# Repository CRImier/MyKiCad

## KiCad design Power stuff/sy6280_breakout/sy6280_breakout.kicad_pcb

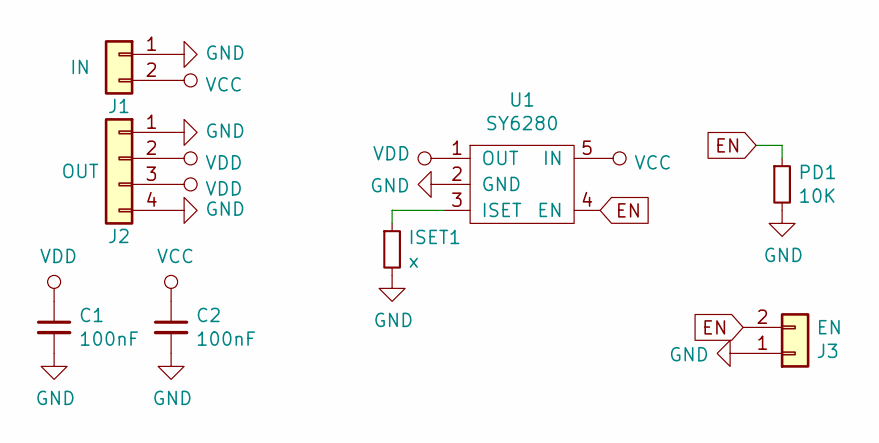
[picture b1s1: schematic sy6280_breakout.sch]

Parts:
C1, C2: 100nF; C_0805_2012Metric
ISET1: x; R_0805_2012Metric_Pad1.15x1.40mm_HandSolder
J1: IN; PinHeader_1x02_P2.54mm_Vertical
J2: OUT; PinHeader_1x04_P2.54mm_Vertical
J3: EN; PinHeader_1x02_P2.54mm_Vertical
PD1: 10K; R_0805_2012Metric_Pad1.15x1.40mm_HandSolder
U1: SY6280; SOT-23-5

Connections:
EN: J3.2, PD1.1, U1.4 (EN)
GND: C1.2, C2.2, ISET1.2, J1.1, J2.1, J2.4, J3.1, PD1.2, U1.2 (GND)
unnamed: ISET1.1, U1.3 (ISET)
VCC: C2.1, J1.2, U1.5 (IN)
VDD: C1.1, J2.2, J2.3, U1.1 (OUT)

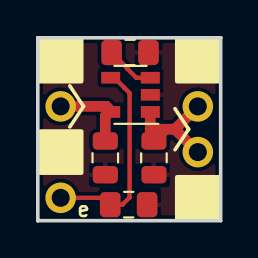
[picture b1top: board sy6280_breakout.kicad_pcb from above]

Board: 2 copper layers, 10.2 x 10.2 mm, 8 parts (0 on the bottom side), 5 nets.

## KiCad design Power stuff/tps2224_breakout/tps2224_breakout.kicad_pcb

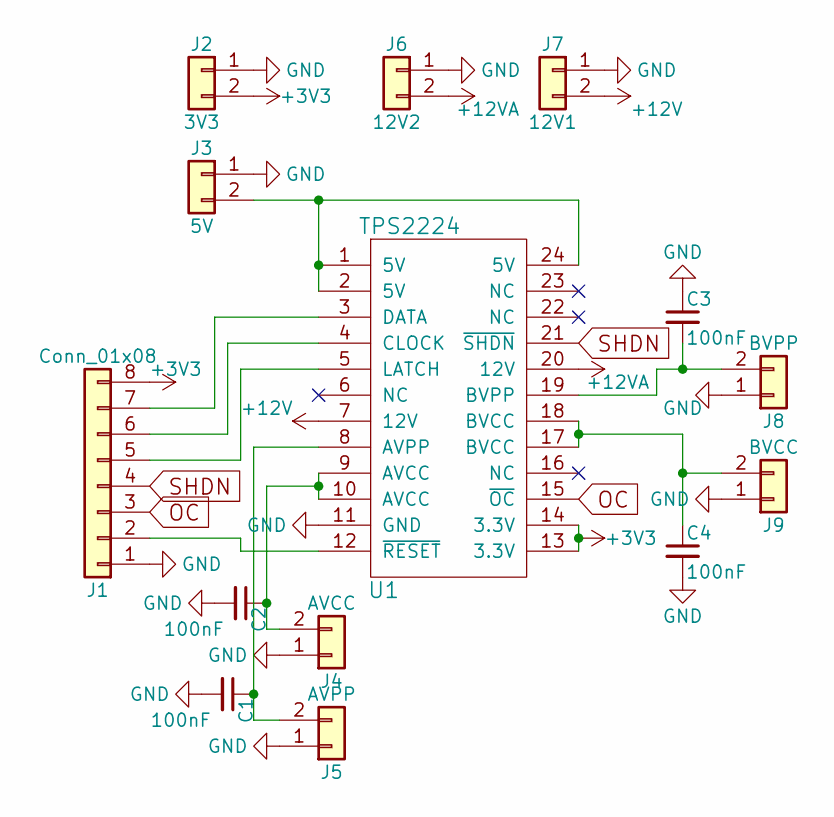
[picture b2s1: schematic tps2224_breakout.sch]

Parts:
C1, C2, C3, C4: 100nF; C_0805
J1: Conn_01x08; Pin_Header_Straight_1x08_Pitch2.54mm
J2: 3V3; Pin_Header_Straight_1x02_Pitch2.54mm
J3: 5V; Pin_Header_Straight_1x02_Pitch2.54mm
J4: AVCC; Pin_Header_Straight_1x02_Pitch2.54mm
J5: AVPP; Pin_Header_Straight_1x02_Pitch2.54mm
J6: 12V2; Pin_Header_Straight_1x02_Pitch2.54mm
J7: 12V1; Pin_Header_Straight_1x02_Pitch2.54mm
J8: BVPP; Pin_Header_Straight_1x02_Pitch2.54mm
J9: BVCC; Pin_Header_Straight_1x02_Pitch2.54mm
U1: TPS2224; TSSOP-24_4.4x7.8mm_Pitch0.65mm

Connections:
+3V3: J1.8, J2.2, U1.13 (3.3V), U1.14 (3.3V)
+12V: J7.2, U1.7 (12V)
+12VA: J6.2, U1.20 (12V)
GND: C1.2, C2.2, C3.1, C4.2, J1.1, J2.1, J3.1, J4.1, J5.1, J6.1, J7.1, J8.1, J9.1, U1.11 (GND)
unnamed: C1.1, J5.2, U1.8 (AVPP)
unnamed: C2.1, J4.2, U1.9 (AVCC), U1.10 (AVCC)
unnamed: C3.2, J8.2, U1.19 (BVPP)
unnamed: C4.1, J9.2, U1.17 (BVCC), U1.18 (BVCC)
unnamed: J1.2, U1.12 (~RESET)
unnamed: J1.5, U1.5 (LATCH)
unnamed: J1.6, U1.4 (CLOCK)
unnamed: J1.7, U1.3 (DATA)
unnamed: J3.2, U1.1 (5V), U1.2 (5V), U1.24 (5V)
OC: J1.3, U1.15 (~OC)
SHDN: J1.4, U1.21 (~SHDN)

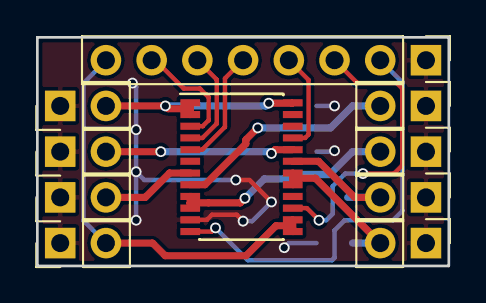
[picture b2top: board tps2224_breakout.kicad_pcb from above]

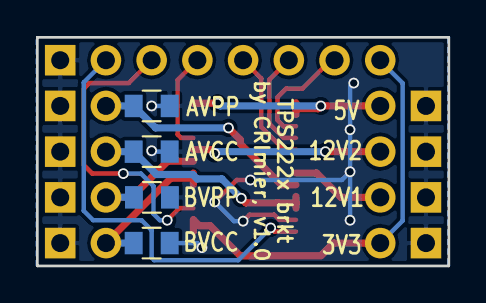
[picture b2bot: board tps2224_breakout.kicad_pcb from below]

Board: 2 copper layers, 22.9 x 12.7 mm, 14 parts (4 on the bottom side), 15 nets.

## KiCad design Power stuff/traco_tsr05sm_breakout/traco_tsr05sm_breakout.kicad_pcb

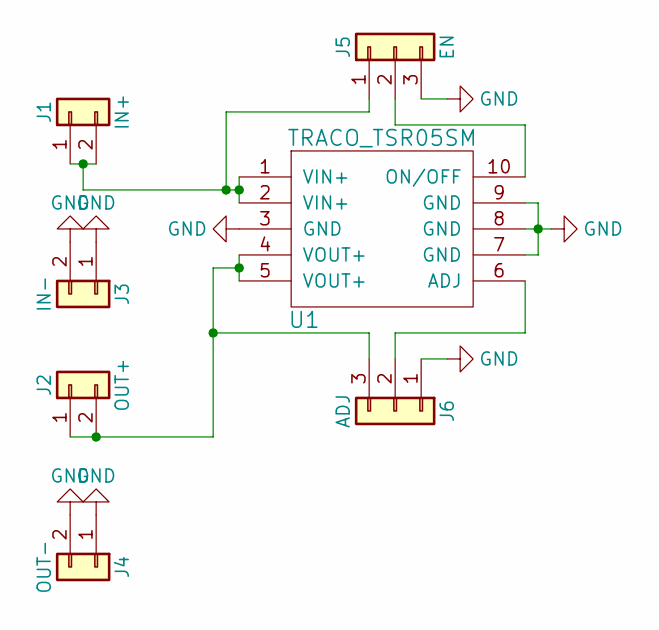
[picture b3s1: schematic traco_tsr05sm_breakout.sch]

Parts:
J1: IN+; WireConnection_2.00mmDrill
J2: OUT+; WireConnection_2.00mmDrill
J3: IN-; WireConnection_2.00mmDrill
J4: OUT-; WireConnection_2.00mmDrill
J5: EN; Pin_Header_Straight_1x03_Pitch2.54mm
J6: ADJ; Pin_Header_Straight_1x03_Pitch2.54mm
U1: TRACO_TSR05SM

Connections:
GND: J3.1, J3.2, J4.1, J4.2, J5.3, J6.1, U1.3 (GND), U1.7 (GND), U1.8 (GND), U1.9 (GND)
unnamed: J1.1, J1.2, J5.1, U1.1 (VIN+), U1.2 (VIN+)
unnamed: J2.1, J2.2, J6.3, U1.4 (VOUT+), U1.5 (VOUT+)
unnamed: J5.2, U1.10 (ON/OFF)
unnamed: J6.2, U1.6 (ADJ)

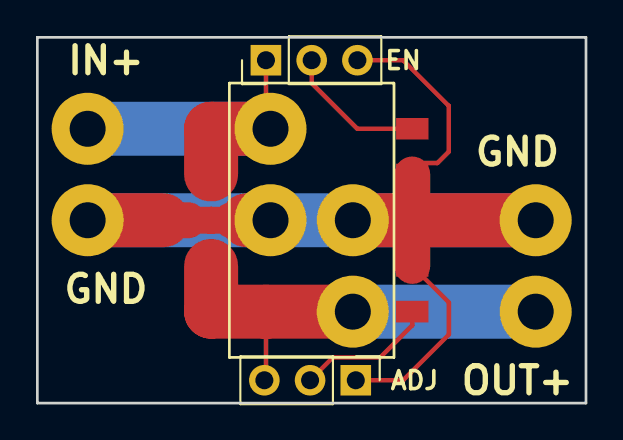
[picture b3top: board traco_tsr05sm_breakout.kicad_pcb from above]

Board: 2 copper layers, 30.5 x 20.3 mm, 7 parts (0 on the bottom side), 5 nets.

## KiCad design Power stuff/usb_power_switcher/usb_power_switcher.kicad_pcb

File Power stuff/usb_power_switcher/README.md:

# USB power switcher

This is a board that switches a USB power signal by using a P-FET to interrupt it. This way,
you can control power to a USB device of your choosing. You can also choose to interrupt the
D- or D+ signals manually, by cutting the jumpers on the bottom of the board.
It has LEDs for output and input power state indication, as well as control signal state.

This board has a MicroUSB input and a USB-A female output. 
It could possibly have a USB-A input plug, but I never tested its polarity.
For now, I personally use the USB-A input for soldering wires to, as a rule.

Jumper signals are arranged in a way that you can use a single 2.54mm jumper to switch the board's state.
There's no overcurrent protection on the board - so be careful.

Signal names are silkscreened on the board's bottom layer.

- PCB size: 36.22*h
- Layer count: 2
- Recommended thickness: t

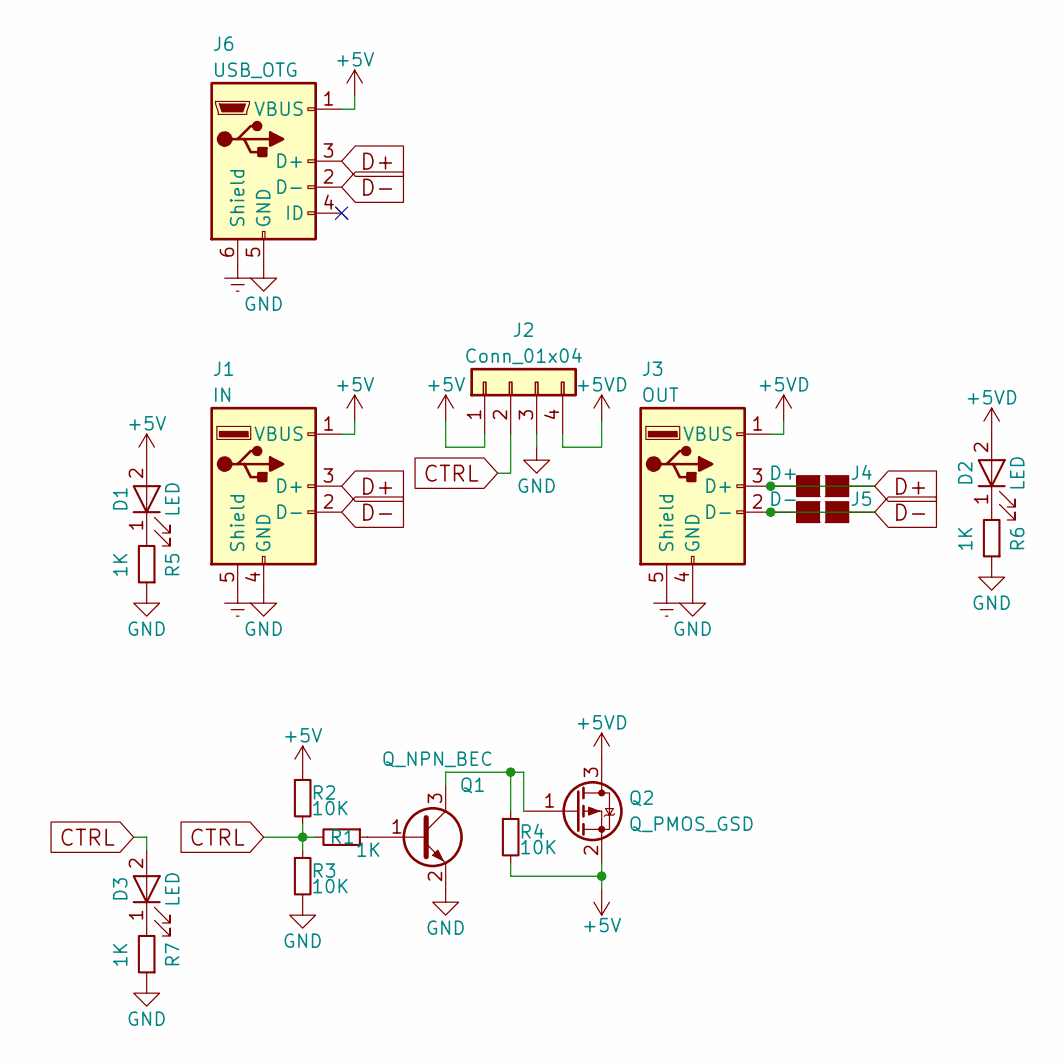
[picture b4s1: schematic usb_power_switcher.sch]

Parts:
D1, D2, D3: LED; LED_0805_HandSoldering
J1: IN; USB_A
J2: Conn_01x04; Pin_Header_Straight_1x04_Pitch2.54mm
J3: OUT; USB_A
J4: D+; GS2_SMALL
J5: D-; GS2_SMALL
J6: USB_OTG; MICROUSB_SIMPLE
Q1: Q_NPN_BEC; SOT-23_Handsoldering
Q2: Q_PMOS_GSD; SOT-23_Handsoldering
R1, R5, R6, R7: 1K; R_0603_HandSoldering
R2, R3, R4: 10K; R_0603_HandSoldering

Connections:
+5V: D1.2 (A), J1.1 (VBUS), J2.1, J6.1 (VBUS), Q2.2 (S), R2.1, R4.2
+5VD: D2.2 (A), J2.4, J3.1 (VBUS), Q2.3 (D)
CTRL: D3.2 (A), J2.2, R1.2, R2.2, R3.1
D+: J1.3 (D+), J3.3 (D+), J4.1 (G1), J4.2 (G2), J6.3 (D+)
D-: J1.2 (D-), J3.2 (D-), J5.1 (G1), J5.2 (G2), J6.2 (D-)
Earth: J1.5 (Shield), J3.5 (Shield), J6.6 (Shield)
GND: J1.4 (GND), J2.3, J3.4 (GND), J6.5 (GND), Q1.2 (E), R3.2, R5.1, R6.1, R7.1
unnamed: D1.1 (K), R5.2
unnamed: D2.1 (K), R6.2
unnamed: D3.1 (K), R7.2
unnamed: Q1.1 (B), R1.1
unnamed: Q1.3 (C), Q2.1 (G), R4.1

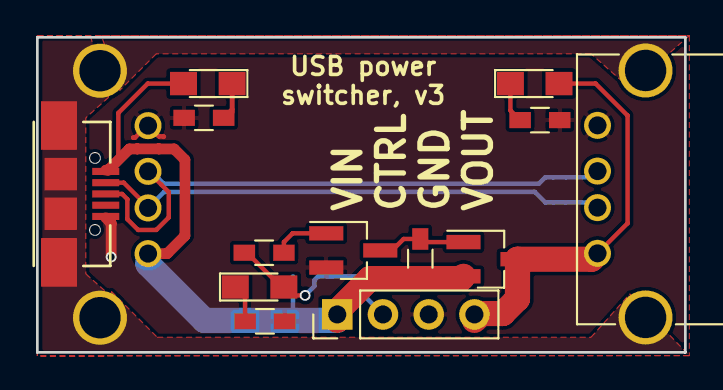
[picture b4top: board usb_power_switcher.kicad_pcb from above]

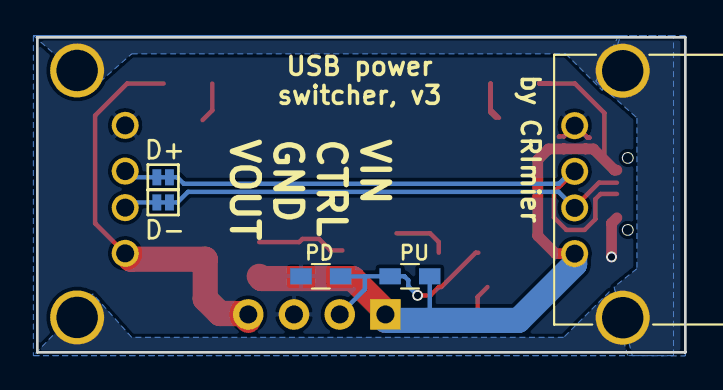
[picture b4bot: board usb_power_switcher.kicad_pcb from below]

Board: 2 copper layers, 36.0 x 17.5 mm, 18 parts (5 on the bottom side), 12 nets.

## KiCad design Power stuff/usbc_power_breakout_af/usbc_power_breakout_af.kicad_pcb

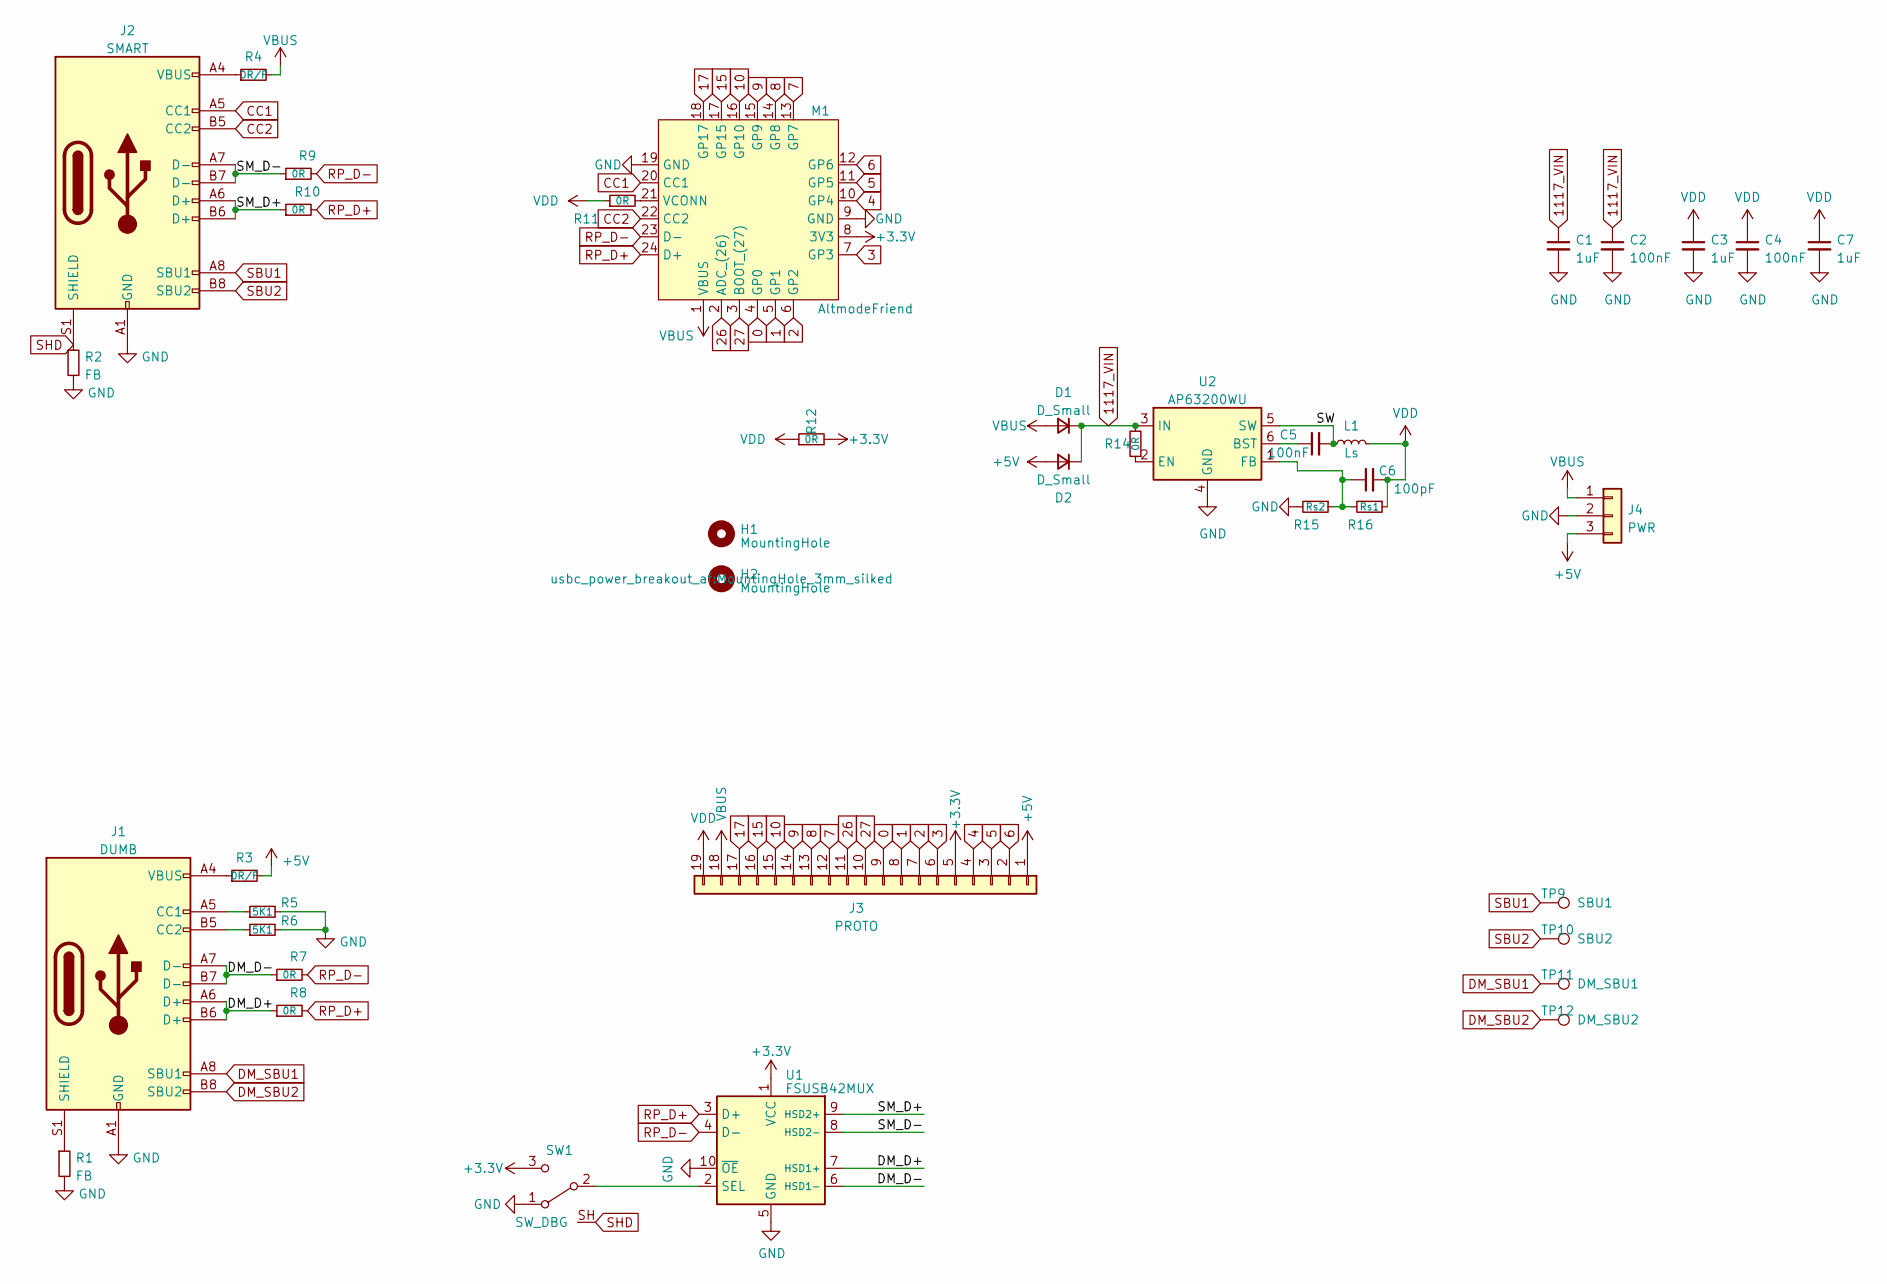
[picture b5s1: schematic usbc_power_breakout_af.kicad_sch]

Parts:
C1, C3, C7: 1uF; C_0805_2012Metric
C2: 100nF; C_0805_2012Metric
C4, C5: 100nF; C_0603_1608Metric
C6: 100pF; C_0603_1608Metric
D1, D2: D_Small; D_SMA
H1, H2: MountingHole; MountingHole_3mm_silked
J1: DUMB; USB_C_Receptacle_HRO_TYPE-C-31-M-12
J2: SMART; USB_C_Receptacle_HRO_TYPE-C-31-M-12
J3: PROTO; PROTO_THT_SMD_4x
J4: PWR; PinHeader_1x03_P2.54mm_Vertical
L1: Ls; L_Bourns-SRN4018
M1: AltmodeFriend; altmode_friend
R1, R2: FB; R_0805_2012Metric
R3, R4: 0R/F; R_0805_2012Metric
R5, R6: 5K1; R_0603_1608Metric
R7, R8, R9, R10, R11, R12, R14: 0R; R_0603_1608Metric
R15: Rs2; R_0603_1608Metric
R16: Rs1; R_0603_1608Metric
SW1: SW_DBG; SW_SPDT_PCM12_SH
TP9: SBU1; TestPoint_THTPad_D1.0mm_Drill0.5mm
TP10: SBU2; TestPoint_THTPad_D1.0mm_Drill0.5mm
TP11: DM_SBU1; TestPoint_THTPad_1.5x1.5mm_Drill0.7mm
TP12: DM_SBU2; TestPoint_THTPad_1.5x1.5mm_Drill0.7mm
U1: FSUSB42MUX; MSOP-10_3x3mm_P0.5mm
U2: AP63200WU; TSOT-23-6

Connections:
0: J3.9, M1.4 (GP0)
1: J3.8, M1.5 (GP1)
2: J3.7, M1.6 (GP2)
3: J3.6, M1.7 (GP3)
4: J3.4, M1.10 (GP4)
5: J3.3, M1.11 (GP5)
6: J3.2, M1.12 (GP6)
7: J3.12, M1.13 (GP7)
8: J3.13, M1.14 (GP8)
9: J3.14, M1.15 (GP9)
10: J3.15, M1.16 (GP10)
15: J3.16, M1.17 (GP15)
17: J3.17, M1.18 (GP17)
26: J3.11, M1.2 (ADC_(26))
27: J3.10, M1.3 (BOOT_(27))
1117_VIN: C1.1, C2.1, D1.1 (K), D2.1 (K), R14.2, U2.3 (IN)
+5V: D2.2 (A), J3.1, J4.3, R3.2
/DM_D+: J1.A6 (D+), J1.B6 (D+), R8.1, U1.7 (HSD1+)
/DM_D-: J1.A7 (D-), J1.B7 (D-), R7.1, U1.6 (HSD1-)
/SM_D+: J2.A6 (D+), J2.B6 (D+), R10.1, U1.9 (HSD2+)
/SM_D-: J2.A7 (D-), J2.B7 (D-), R9.1, U1.8 (HSD2-)
/SW: C5.2, L1.1, U2.5 (SW)
CC1: J2.A5 (CC1), M1.20 (CC1)
CC2: J2.B5 (CC2), M1.22 (CC2)
DM_SBU1: J1.A8 (SBU1), TP11.1
DM_SBU2: J1.B8 (SBU2), TP12.1
GND: C1.2, C2.2, C3.2, C4.2, C7.2, J1.A1 (GND), J1.A12 (GND), J1.B1 (GND), J1.B12 (GND), J2.A1 (GND), J2.A12 (GND), J2.B1 (GND), J2.B12 (GND), J4.2, M1.9 (GND), M1.19 (GND), R1.2, R2.2, R5.2, R6.2, R15.2, SW1.1 (A), U1.5 (GND), U1.10 (~OE), U2.4 (GND)
unnamed: J1.A5 (CC1), R5.1
unnamed: J1.B5 (CC2), R6.1
unnamed: J1.S1 (SHIELD), R1.1
unnamed: J1.A4 (VBUS), J1.A9 (VBUS), J1.B4 (VBUS), J1.B9 (VBUS), R3.1
unnamed: J2.A4 (VBUS), J2.A9 (VBUS), J2.B4 (VBUS), J2.B9 (VBUS), R4.1
unnamed: M1.21 (VCONN), R11.2
unnamed: SW1.2 (B), U1.2 (SEL)
unnamed: C5.1, U2.6 (BST)
unnamed: R14.1, U2.2 (EN)
unnamed: C6.1, R15.1, R16.2, U2.1 (FB)
RP_D+: M1.24 (D+), R8.2, R10.2, U1.3 (D+)
RP_D-: M1.23 (D-), R7.2, R9.2, U1.4 (D-)
SBU1: J2.A8 (SBU1), TP9.1
SBU2: J2.B8 (SBU2), TP10.1
SHD: J2.S1 (SHIELD), R2.1, SW1.SH
VBUS: D1.2 (A), J3.18, J4.1, M1.1 (VBUS), R4.2
VDD: C3.1, C4.1, C6.2, C7.1, J3.19, L1.2, R11.1, R12.1, R16.1

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
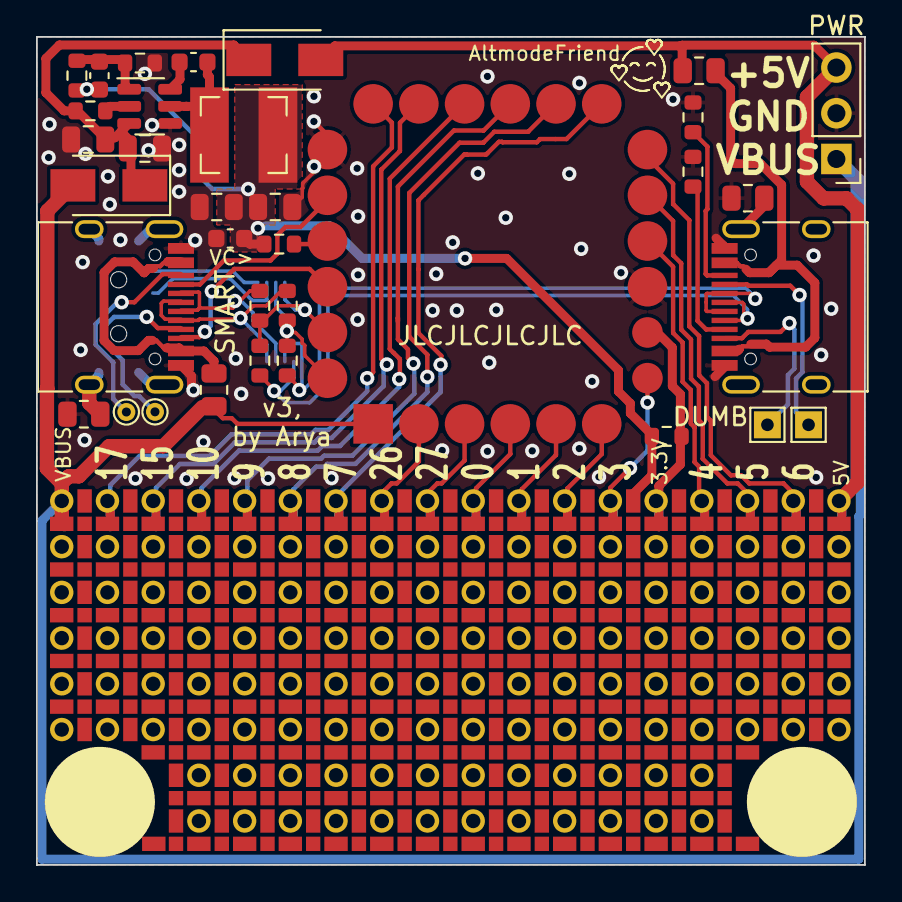
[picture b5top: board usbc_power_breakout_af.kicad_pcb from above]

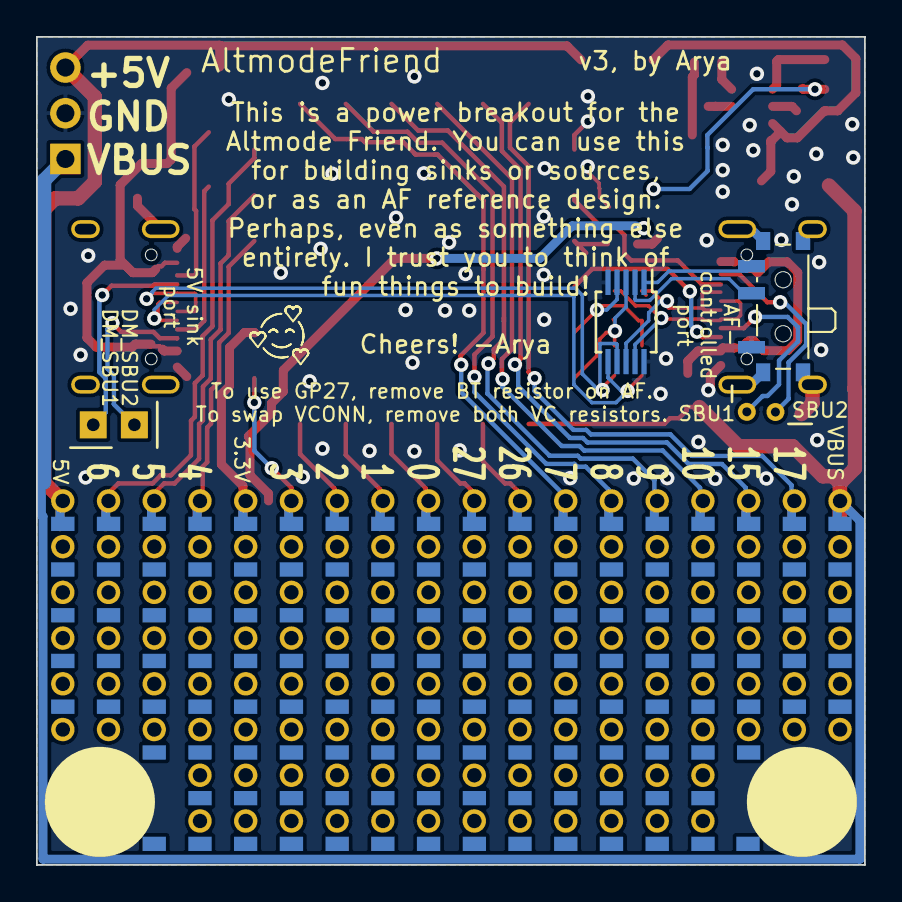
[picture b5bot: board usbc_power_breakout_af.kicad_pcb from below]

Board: 2 copper layers, 46.0 x 46.0 mm, 39 parts (2 on the bottom side), 46 nets.

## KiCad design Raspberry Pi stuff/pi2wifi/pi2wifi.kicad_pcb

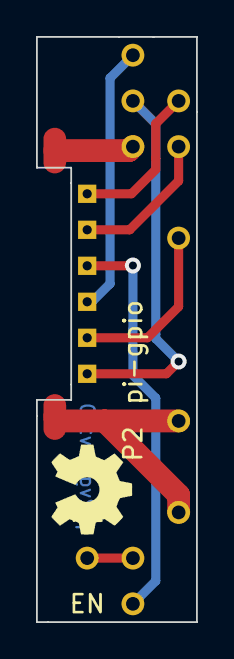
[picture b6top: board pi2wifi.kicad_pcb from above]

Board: 2 copper layers, 8.9 x 32.5 mm, 3 parts (0 on the bottom side), 9 nets.

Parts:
P1: EN; TP
P2: pi-gpio
U1: ESP-12F; ESP-12-F

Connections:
unnamed: P1.1, P2.35
unnamed: P2.37, U1.11
unnamed: P2.16, U1.9
unnamed: P2.18, U1.10
unnamed: P2.15, U1.14
unnamed: P2.13, U1.12
unnamed: P2.22, U1.13
unnamed: P2.30, P2.34, U1.15
unnamed: P2.17, U1.8

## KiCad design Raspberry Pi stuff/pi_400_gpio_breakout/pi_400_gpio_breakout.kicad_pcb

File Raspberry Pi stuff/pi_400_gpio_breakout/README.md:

# Raspberry Pi 400 GPIO adapter board

This board is designed to be plugged into a Raspberry Pi 400 and allow to plug a HAT into your Pi 400 the same way that
you'd plug a hat onto your Raspberry Pi. Apart from that, it also has 2 QWIIC connectors, one 5-pin I2C pin header
with an extra GPIO (same pinout as Pi pins 1-9) and one custom-pinout pin header with SPI, I2S, 3.3V and 5V (same pinout
as the ZeroPhone expansion header pinout).

For ease of routing purposes, this is a 4-layer board, but it could probably be re-routed into a 2-layer board
if someone were willing to spend time on that. Sadly, the Pi 400 GPIO header pin assignment doesn't make for straightforward routing
when it comes to the connector placement I've devised, and I don't need this to be a 2-layer board at the moment.
Let me know if you want to make it into one - I can help you understand how to route it.

For custom connectors with I2C, SPI and I2S, signal names are silkscreened on the board's top layer, including the QWIIC pinout.

v1.0:
    - Initial commit
v2
    - stencil remains the same as in v1.0
    - enlarged mounting holes to 3.2mm
    - small routing mistakes fixed
    - changed I2C header footprint and moved it closer to the board edge

- PCB size: 55*60mm
- Layer count: 4
- Recommended thickness: 1.6mm (it's a relatively large board and has to hold up well to bending)

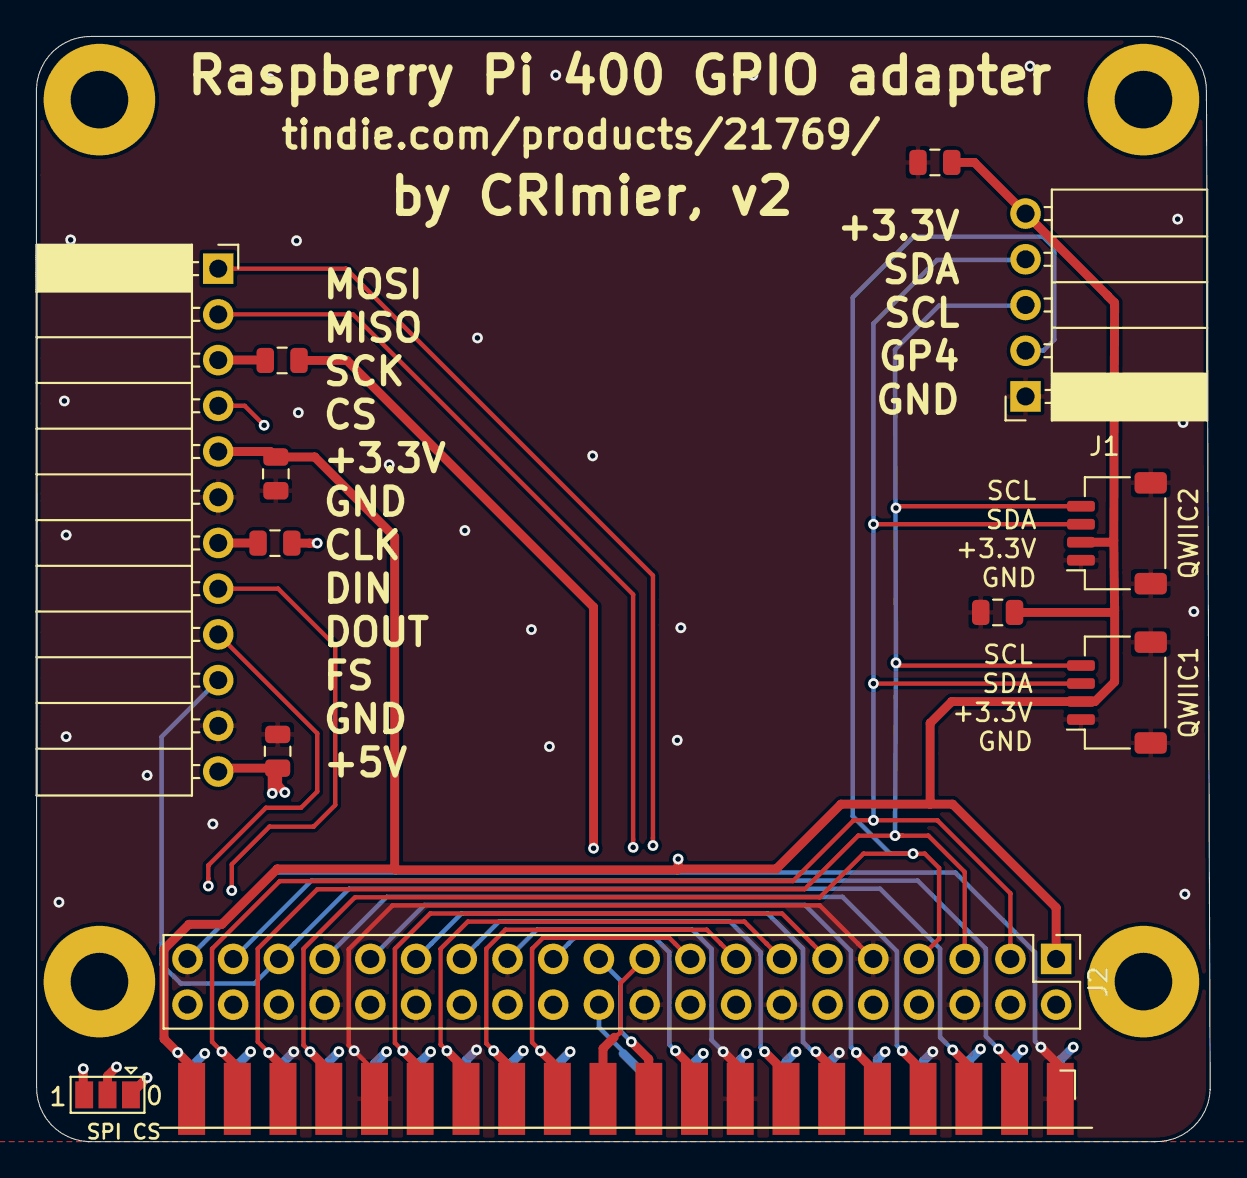
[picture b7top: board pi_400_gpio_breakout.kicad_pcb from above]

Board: 4 copper layers, 65.2 x 61.4 mm, 14 parts (0 on the bottom side), 34 nets.

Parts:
C1, C2, C3, C4: 100nF; C_0805_2012Metric
J1: I2C; PinSocket_1x05_P2.54mm_Horizontal
J2: RPI_IN; PinHeader_2x20_P2.54mm_Vertical
J3: SPI_I2S; PinSocket_1x12_P2.54mm_Horizontal
J4: QWIIC1; JST_SH_SM04B-SRSS-TB_1x04-1MP_P1.00mm_Horizontal
J5: Raspberry_Pi_2_3; RASPBERRY_PI_HAT
J5#2: RPI_IN; Side_2x20_Connector_SMD
J6: QWIIC2; JST_SH_SM04B-SRSS-TB_1x04-1MP_P1.00mm_Horizontal
JP1: SPI CS; SolderJumper-3_P1.3mm_Open_Pad1.0x1.5mm
R1, R2: 47R; R_0805_2012Metric

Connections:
+3V3: C1.1, C2.1, C3.1, J1.5, J2.1, J2.17, J3.5, J4.2, J5#2.1, J5#2.17, J6.2
+5V: C4.1, J2.2, J2.4, J3.12, J5#2.2, J5#2.4
/CS: J3.4, JP1.2
/CS0: J2.24, J5#2.24, JP1.1
/CS1: J2.26, J5#2.26, JP1.3
/GP4: J1.2, J2.7, J5#2.7
/MISO: J2.21, J3.2, J5#2.21
/MOSI: J2.19, J3.1, J5#2.19
/PCM_CLK: J2.18, J5#2.18, R2.1
/PCM_DIN: J2.38, J3.8, J5#2.38
/PCM_DOUT: J2.40, J3.9, J5#2.40
/PCM_FS: J2.35, J3.10, J5#2.35
/SCK: J2.23, J5#2.23, R1.1
/SCL: J1.3, J2.5, J4.4, J5#2.5, J6.4
/SDA: J1.4, J2.3, J4.3, J5#2.3, J6.3
GND: C1.2, C2.2, C3.2, C4.2, J1.1, J2.6, J2.9, J2.14, J2.20, J2.25, J2.30, J2.34, J2.39, J3.6, J3.11, J4.1, J4.MP, J5#2.6, J5#2.9, J5#2.14, J5#2.20, J5#2.25, J5#2.30, J5#2.34, J5#2.39, J6.1, J6.MP
unnamed: J2.8, J5#2.8
unnamed: J2.10, J5#2.10
unnamed: J2.11, J5#2.11
unnamed: J2.12, J5#2.12
unnamed: J2.13, J5#2.13
unnamed: J2.15, J5#2.15
unnamed: J2.16, J5#2.16
unnamed: J2.22, J5#2.22
unnamed: J2.27, J5#2.27
unnamed: J2.28, J5#2.28
unnamed: J2.29, J5#2.29
unnamed: J2.31, J5#2.31
unnamed: J2.32, J5#2.32
unnamed: J2.33, J5#2.33
unnamed: J2.36, J5#2.36
unnamed: J2.37, J5#2.37
unnamed: J3.3, R1.2
unnamed: J3.7, R2.2

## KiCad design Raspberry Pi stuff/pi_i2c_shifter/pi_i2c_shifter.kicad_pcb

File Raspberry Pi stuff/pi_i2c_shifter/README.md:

# Pi I2C shifter

This board level-shifts the I2C header and the GPIO to 5V using a N-FET level shifter approach.
It can be mounted to the Pi in two different orientation, so that the 5V I2C header can either stick
outside of the Pi outline or stay inside of it for a compact build.

Pin headers are arranged in a way that this board can be plugged into a breadboard from the I2C side.
The pin headers also have staggered holes so that you can press-fit the board onto headers and
have it work without soldering, again, from any side.
Signal names are silkscreened on the bottom of the board.

- PCB size: 21x14
- Layer count: 2
- Recommended thickness: 0.6mm/0.8mm (to be thin enough so that shields can be plugged on top of it)

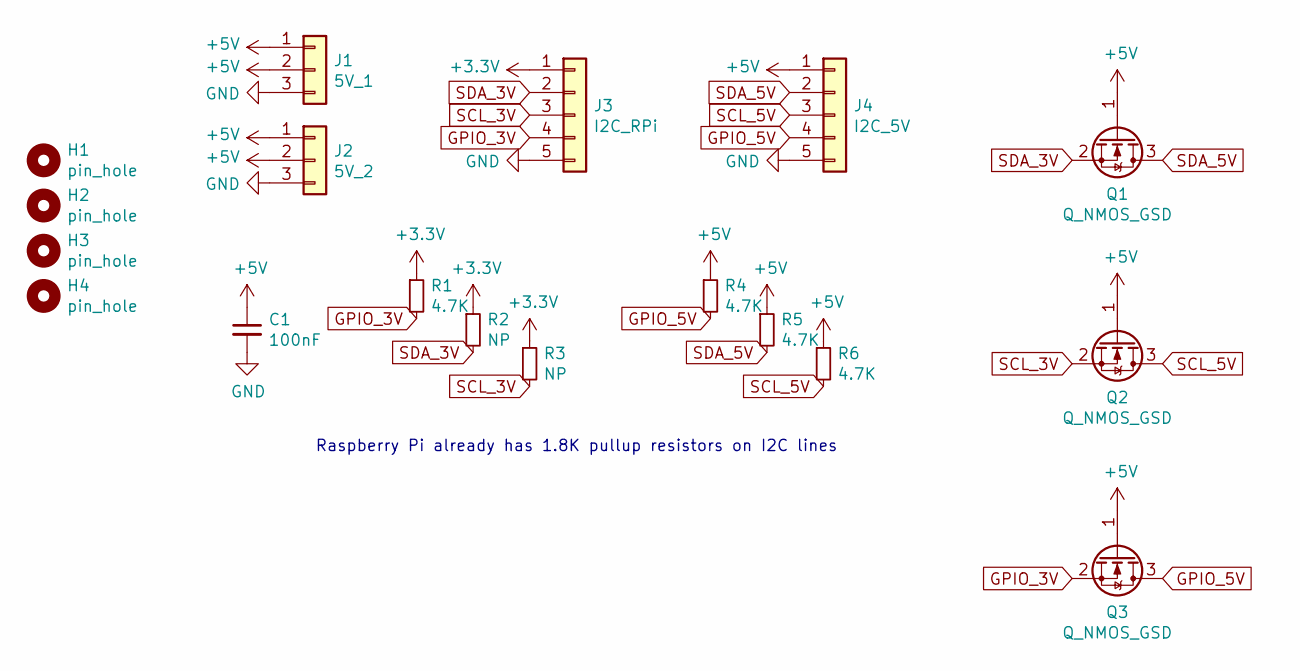
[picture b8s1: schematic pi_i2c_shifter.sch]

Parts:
C1: 100nF; C_0805_2012Metric
H1, H2, H3, H4: pin_hole; MountingHole_2.1mm
J1: 5V_1; PinHeader_1x03_P2.54mm_Vertical
J2: 5V_2; PinHeader_1x03_P2.54mm_Vertical
J3: I2C_RPi; PinHeader_1x05_P2.54mm_Vertical
J4: I2C_5V; PinHeader_1x05_P2.54mm_Vertical
Q1, Q2, Q3: Q_NMOS_GSD; SOT-23
R1, R4, R5, R6: 4.7K; R_0805_2012Metric
R2, R3: NP; R_0805_2012Metric

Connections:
+3V3: J3.1, R1.1, R2.1, R3.1
+5V: C1.1, J1.1, J1.2, J2.1, J2.2, J4.1, Q1.1 (G), Q2.1 (G), Q3.1 (G), R4.1, R5.1, R6.1
GND: C1.2, J1.3, J2.3, J3.5, J4.5
GPIO_3V: J3.4, Q3.2 (S), R1.2
GPIO_5V: J4.4, Q3.3 (D), R4.2
SCL_3V: J3.3, Q2.2 (S), R3.2
SCL_5V: J4.3, Q2.3 (D), R6.2
SDA_3V: J3.2, Q1.2 (S), R2.2
SDA_5V: J4.2, Q1.3 (D), R5.2

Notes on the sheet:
Raspberry Pi already has 1.8K pullup resistors on I2C lines

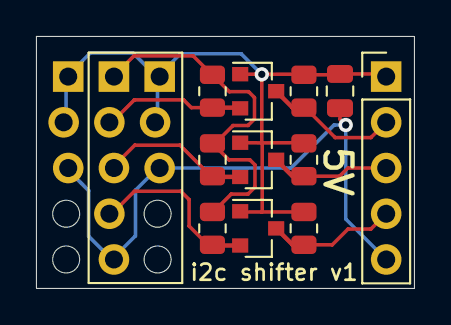
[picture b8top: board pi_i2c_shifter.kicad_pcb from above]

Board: 2 copper layers, 21.0 x 14.0 mm, 18 parts (0 on the bottom side), 9 nets.
